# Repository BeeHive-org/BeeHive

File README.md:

# BeeHive - a flexible platform for connecting different sensors and actuators

## Intro

This project started as a collaboration between [Ihor Sobianin](https://github.com/isobianin/) and [Andre Chagas](https://github.com/amchagas/), after some chats about improving the [FlyPi design](https://github.com/amchagas/flypi). 

## Hardware 

The idea here is to make a very flexible hardware system that is easy to expand/customize for lab applications. The very initial implementation consists of:
- a hub PCB - which contains:
   -  2 voltage regulators that step down voltage from 12V to 5V and supply these 3 voltages to specific pins throughout the board.
   -  a central slot for an [ESP32 WROOM](https://www.espressif.com/sites/default/files/documentation/esp32-wroom-32_datasheet_en.pdf) and the breakout of all its pins into JST connectors.
   - Two Mikroe MikroBus connectors (https://www.mikroe.com/mikrobus).
   - Two Sparkfun Qwiic connectore (https://www.sparkfun.com/qwiic).
   - A 3.3V onboard voltage regulator.

-  4 switch array with an [TPIC6B595 shift register](https://www.ti.com/lit/ds/symlink/tpic6b595.pdf) and transistors.

-  8 switch array with an [TPIC6B595 shift register](https://www.ti.com/lit/ds/symlink/tpic6b595.pdf) and transistors.

-  12V5A breakout which is based on simple barrel jack connector and JST connectors

-  power supply which are based on the [LM2596 T5](https://www.ti.com/lit/ds/symlink/lm2596.pdf) a step down switching regulator
For more details see [current design](#the-current-design) section below.  

## Software

On the software side of things we are initially running micropython, as this will offer a low entry barrier for researchers (as Python is more and more the chosen language for much of the scientific stack).

- The current implementation runs stock micropython with [OSC library](https://github.com/SpotlightKid/micropython-osc) for communication, as this will allow easy integration with [Bonsai-RX](https://bonsai-rx.org/), a powerful piece of software that has integrations with other interesting open source tools for science, such as [open ephys](https://open-ephys.org/), [DeepLab Cut](http://www.mousemotorlab.org/deeplabcut) and other proprietary but useful tools, like high speed cameras, National Instruments DAQ systems. 

- The main wish software wise for this project is to make it compatible with [Labthings](https://github.com/labthings).

---

## The current design

### The main hub:

#### Schematics

#### PCB

### The power supply module:

#### Schematics

#### PCB

### The transistor-switch hub for 8 devices:

#### Schematics

#### PCB

---

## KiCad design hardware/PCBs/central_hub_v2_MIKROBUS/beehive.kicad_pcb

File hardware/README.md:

In this folder users & collaborators will find designs and considerations about the hardware parts being developed in this project. 

### hub_PCB:
- the central part of the system, is mainly a breakout board for the ESP32 being used and two built in power supplies. 

The pin mapping of the ESP32 controller and our board can be seen here:

Using table 2 of this [manual](https://www.espressif.com/sites/default/files/documentation/esp32-wroom-32_datasheet_en.pdf) we can see all the options for each pin.

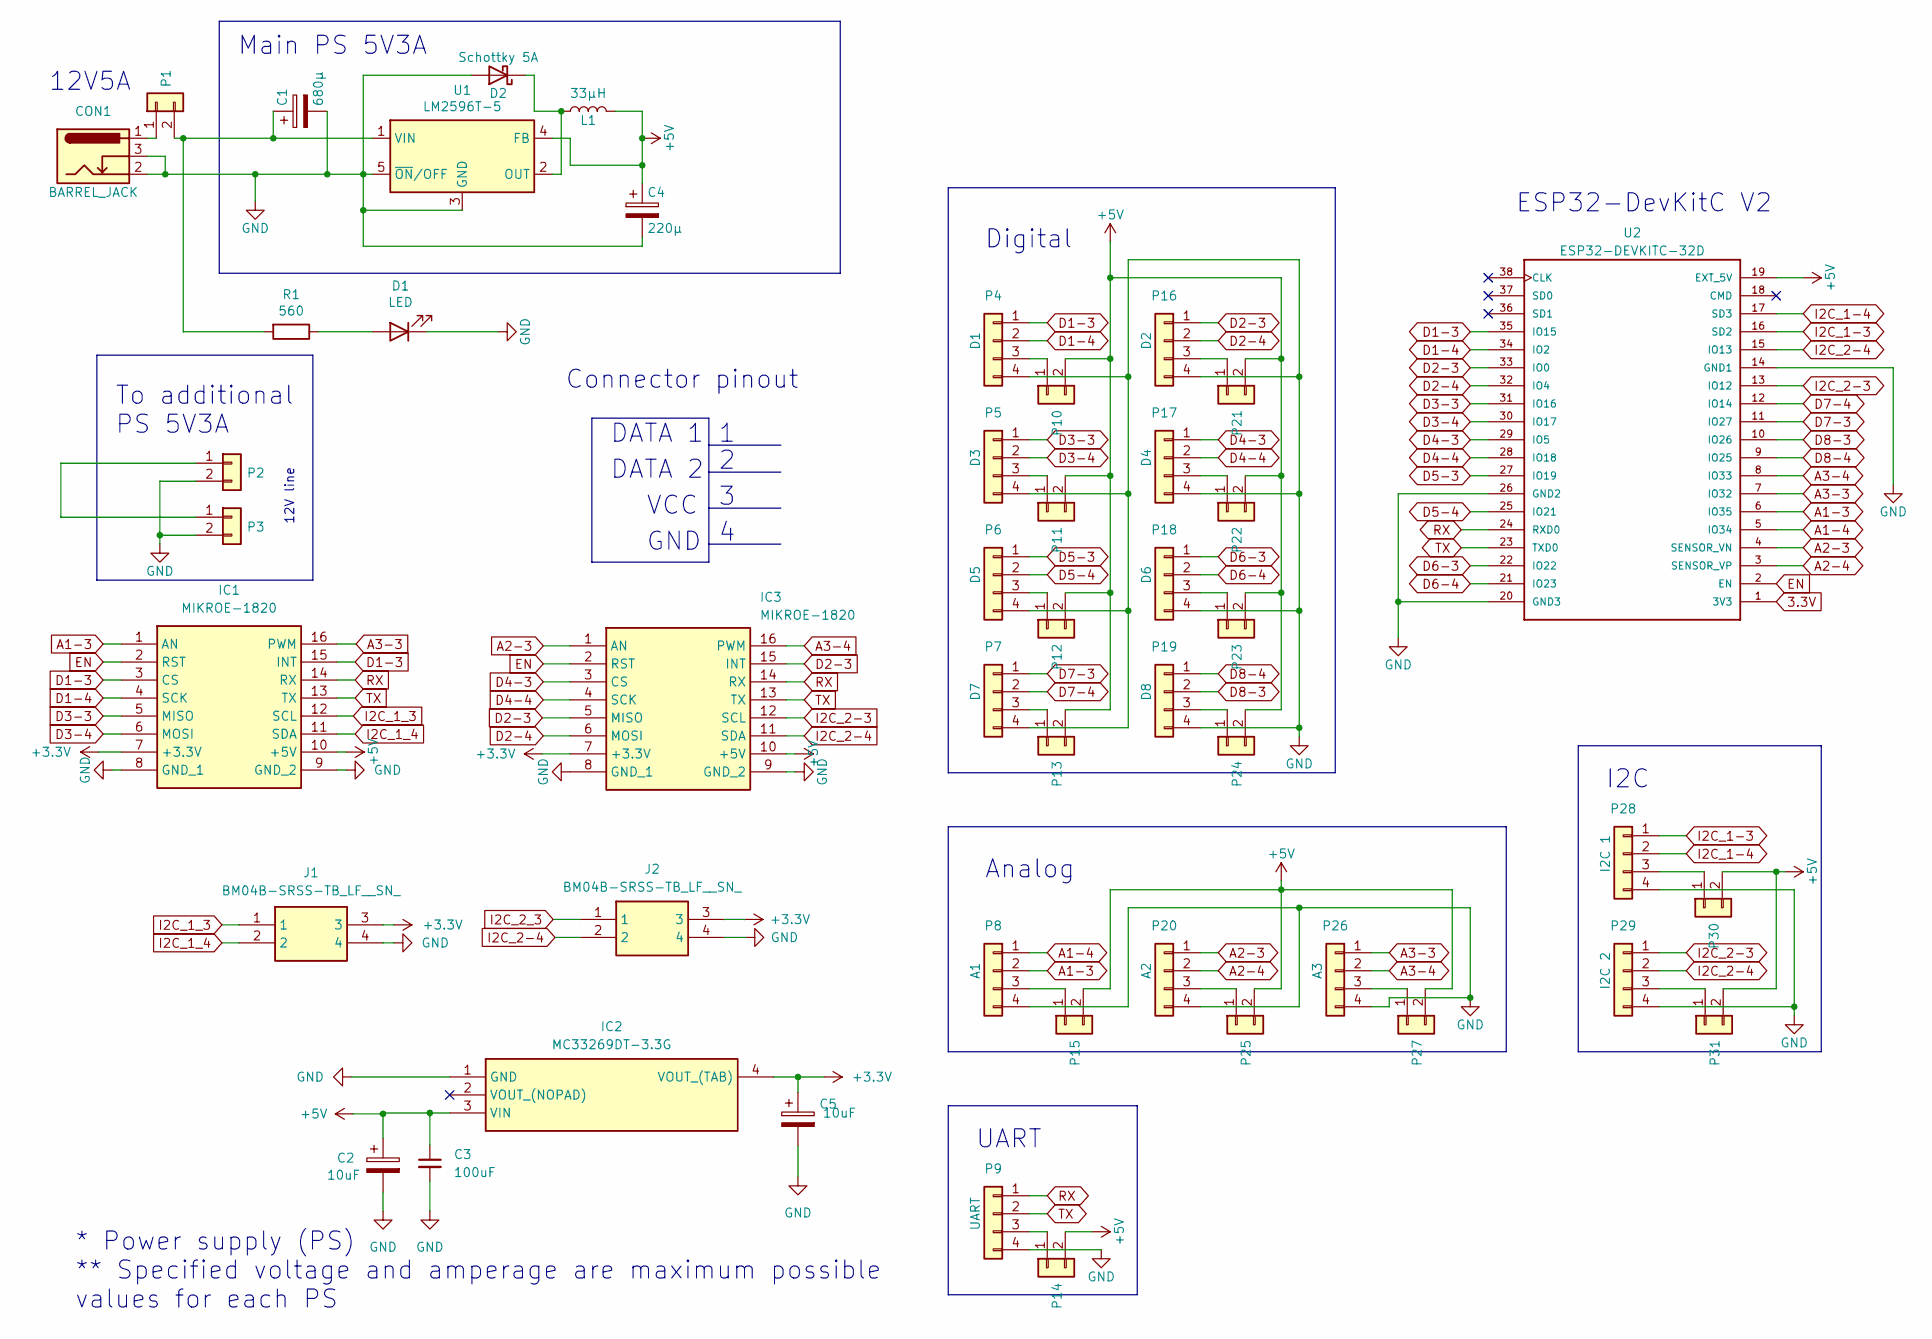
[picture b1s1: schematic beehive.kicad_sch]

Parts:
C1: 680µ; C_Radial_D10_L21_P5
C2, C5: 10uF; C_1206_3216Metric_Pad1.33x1.80mm_HandSolder
C3: 100uF; C_1206_3216Metric_Pad1.33x1.80mm_HandSolder
C4: 220µ; C_Radial_D8_L13_P3.8
CON1: BARREL_JACK; BarrelJack_Horizontal
D1: LED; LED_D3.0mm
D2: Schottky 5A; Diode_DO-201AD_Horizontal_RM15
IC1, IC3: MIKROE-1820; MIKROE1820; Mouser Part Number 932-MIKROE-1820
IC2: MC33269DT-3.3G; TO229P990X238-4N; Mouser Part Number 863-MC33269DT-3.3G
J1, J2: BM04B-SRSS-TB_LF__SN_; SM04B-SRSS-TB_LFSN_; Manufacturer_Part_Number BM04B-SRSS-TB(LF)(SN)
L1: 33µH; Neosid_Inductor_MA-Bs75
P1, P2, P3, P10, P11, P12, P13, P14, P15, P21, P22, P23, P24, P25, P27, P30, P31: Conn_01x02; JST_XH_B2B-XH-A_1x02_P2.50mm_Vertical
P4: D1; JST_XH_B04B-XH-A_04x2.50mm_Straight
P5: D3; JST_XH_B04B-XH-A_04x2.50mm_Straight
P6: D5; JST_XH_B04B-XH-A_04x2.50mm_Straight
P7: D7; JST_XH_B04B-XH-A_04x2.50mm_Straight
P8: A1; JST_XH_B04B-XH-A_04x2.50mm_Straight
P9: UART; JST_XH_B04B-XH-A_04x2.50mm_Straight
P16: D2; JST_XH_B04B-XH-A_04x2.50mm_Straight
P17: D4; JST_XH_B04B-XH-A_04x2.50mm_Straight
P18: D6; JST_XH_B04B-XH-A_04x2.50mm_Straight
P19: D8; JST_XH_B04B-XH-A_04x2.50mm_Straight
P20: A2; JST_XH_B04B-XH-A_04x2.50mm_Straight
P26: A3; JST_XH_B04B-XH-A_04x2.50mm_Straight
P28: I2C 1; JST_XH_B04B-XH-A_04x2.50mm_Straight
P29: I2C 2; JST_XH_B04B-XH-A_04x2.50mm_Straight
R1: 560; R_Box_L13.0mm_W4.0mm_P9.00mm
U1: LM2596T-5; TO-220-5_P3.4x3.7mm_StaggerOdd_Lead3.8mm_Vertical
U2: ESP32-DEVKITC-32D; MODULE_ESP32-DEVKITC-32D

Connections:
3.3V: U2.1 (3V3)
+3.3V: C5.1, IC1.7 (+3.3V), IC2.4 (VOUT_(TAB)), IC3.7 (+3.3V), J1.3, J2.3
A1-3: IC1.1 (AN), P8.2, U2.6 (IO35)
A1-4: P8.1, U2.5 (IO34)
A2-3: IC3.1 (AN), P20.1, U2.4 (SENSOR_VN)
A2-4: P20.2, U2.3 (SENSOR_VP)
A3-3: IC1.16 (PWM), P26.1, U2.7 (IO32)
A3-4: IC3.16 (PWM), P26.2, U2.8 (IO33)
D1-3: IC1.3 (CS), IC1.15 (INT), P4.1, U2.35 (IO15)
D1-4: IC1.4 (SCK), P4.2, U2.34 (IO2)
D2-3: IC3.5 (MISO), IC3.15 (INT), P16.1, U2.33 (IO0)
D2-4: IC3.6 (MOSI), P16.2, U2.32 (IO4)
D3-3: IC1.5 (MISO), P5.1, U2.31 (IO16)
D3-4: IC1.6 (MOSI), P5.2, U2.30 (IO17)
D4-3: IC3.3 (CS), P17.1, U2.29 (IO5)
D4-4: IC3.4 (SCK), P17.2, U2.28 (IO18)
D5-3: P6.1, U2.27 (IO19)
D5-4: P6.2, U2.25 (IO21)
D6-3: P18.1, U2.22 (IO22)
D6-4: P18.2, U2.21 (IO23)
D7-3: P7.1, U2.11 (IO27)
D7-4: P7.2, U2.12 (IO14)
D8-3: P19.2, U2.10 (IO26)
D8-4: P19.1, U2.9 (IO25)
EN: IC1.2 (RST), IC3.2 (RST), U2.2 (EN)
GND: C1.2, C2.2, C3.2, C4.2, C5.2, CON1.2, CON1.3, D1.1 (K), D2.2 (A), IC1.8 (GND_1), IC1.9 (GND_2), IC2.1 (GND), IC3.8 (GND_1), IC3.9 (GND_2), J1.4, J2.4, P2.2, P3.2, P4.4, P5.4, P6.4, P7.4, P8.4, P9.4, P16.4, P17.4, P18.4, P19.4, P20.4, P26.4, P28.4, P29.4, U1.3 (GND), U1.5 (~ON/OFF), U2.14 (GND1), U2.20 (GND3), U2.26 (GND2)
I2C_1-3: P28.1, U2.16 (SD2)
I2C_1-4: P28.2, U2.17 (SD3)
I2C_1_3: IC1.12 (SCL), J1.1
I2C_1_4: IC1.11 (SDA), J1.2
I2C_2-3: IC3.12 (SCL), P29.1, U2.13 (IO12)
I2C_2-4: IC3.11 (SDA), J2.2, P29.2, U2.15 (IO13)
I2C_2_3: J2.1
unnamed: D1.2 (A), R1.1
unnamed: D2.1 (K), L1.1, U1.2 (OUT)
unnamed: CON1.1, P1.1
unnamed: P2.1, P3.1
unnamed: P4.3, P10.1
unnamed: P5.3, P11.1
unnamed: P6.3, P12.1
unnamed: P7.3, P13.1
unnamed: P9.3, P14.1
unnamed: P8.3, P15.1
unnamed: P16.3, P21.1
unnamed: P17.3, P22.1
unnamed: P18.3, P23.1
unnamed: P19.3, P24.1
unnamed: P20.3, P25.1
unnamed: P26.3, P27.1
unnamed: P28.3, P30.1
unnamed: P29.3, P31.1
RX: IC1.14 (RX), IC3.14 (RX), P9.1, U2.24 (RXD0)
TX: IC1.13 (TX), IC3.13 (TX), P9.2, U2.23 (TXD0)

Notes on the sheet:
Connector pinout
12V line
To additional PS 5V3A
VCC
Analog
12V5A
DATA 1
GND
ESP32-DevKitC V2
Main PS 5V3A
* Power supply (PS) ** Specified voltage and amperage are maximum possible values for each PS
DATA 2
I2C
UART
Digital

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
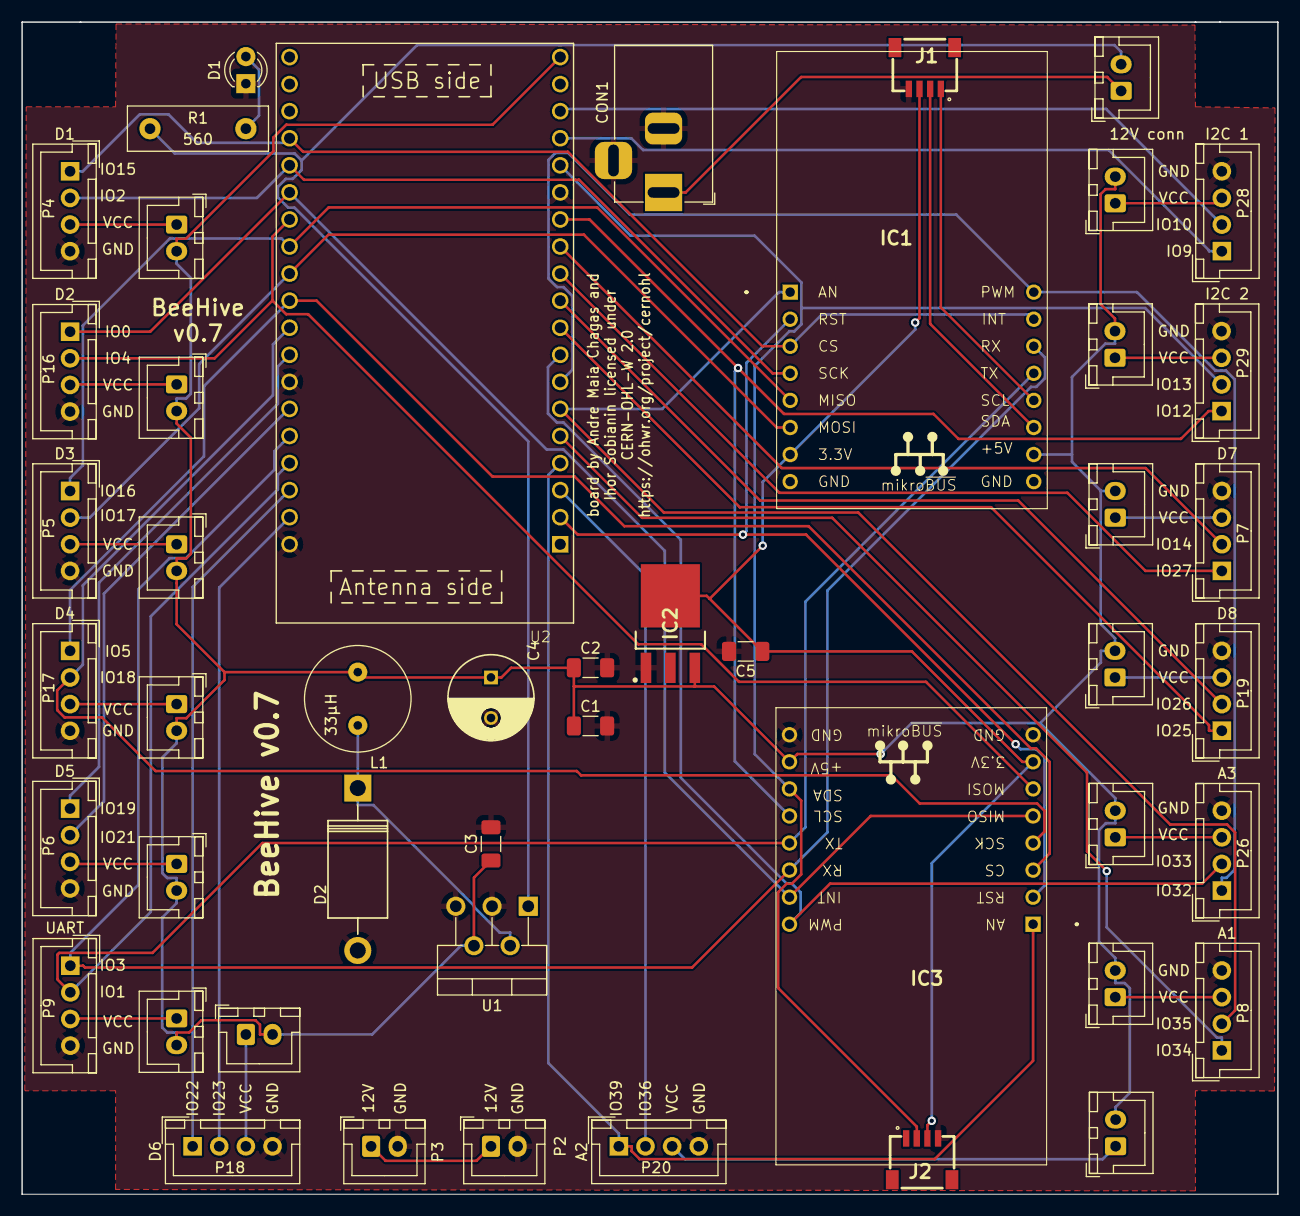
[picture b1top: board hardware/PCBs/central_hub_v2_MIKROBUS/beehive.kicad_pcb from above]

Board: 2 copper layers, 117.8 x 110.0 mm, 48 parts (0 on the bottom side), 53 nets.

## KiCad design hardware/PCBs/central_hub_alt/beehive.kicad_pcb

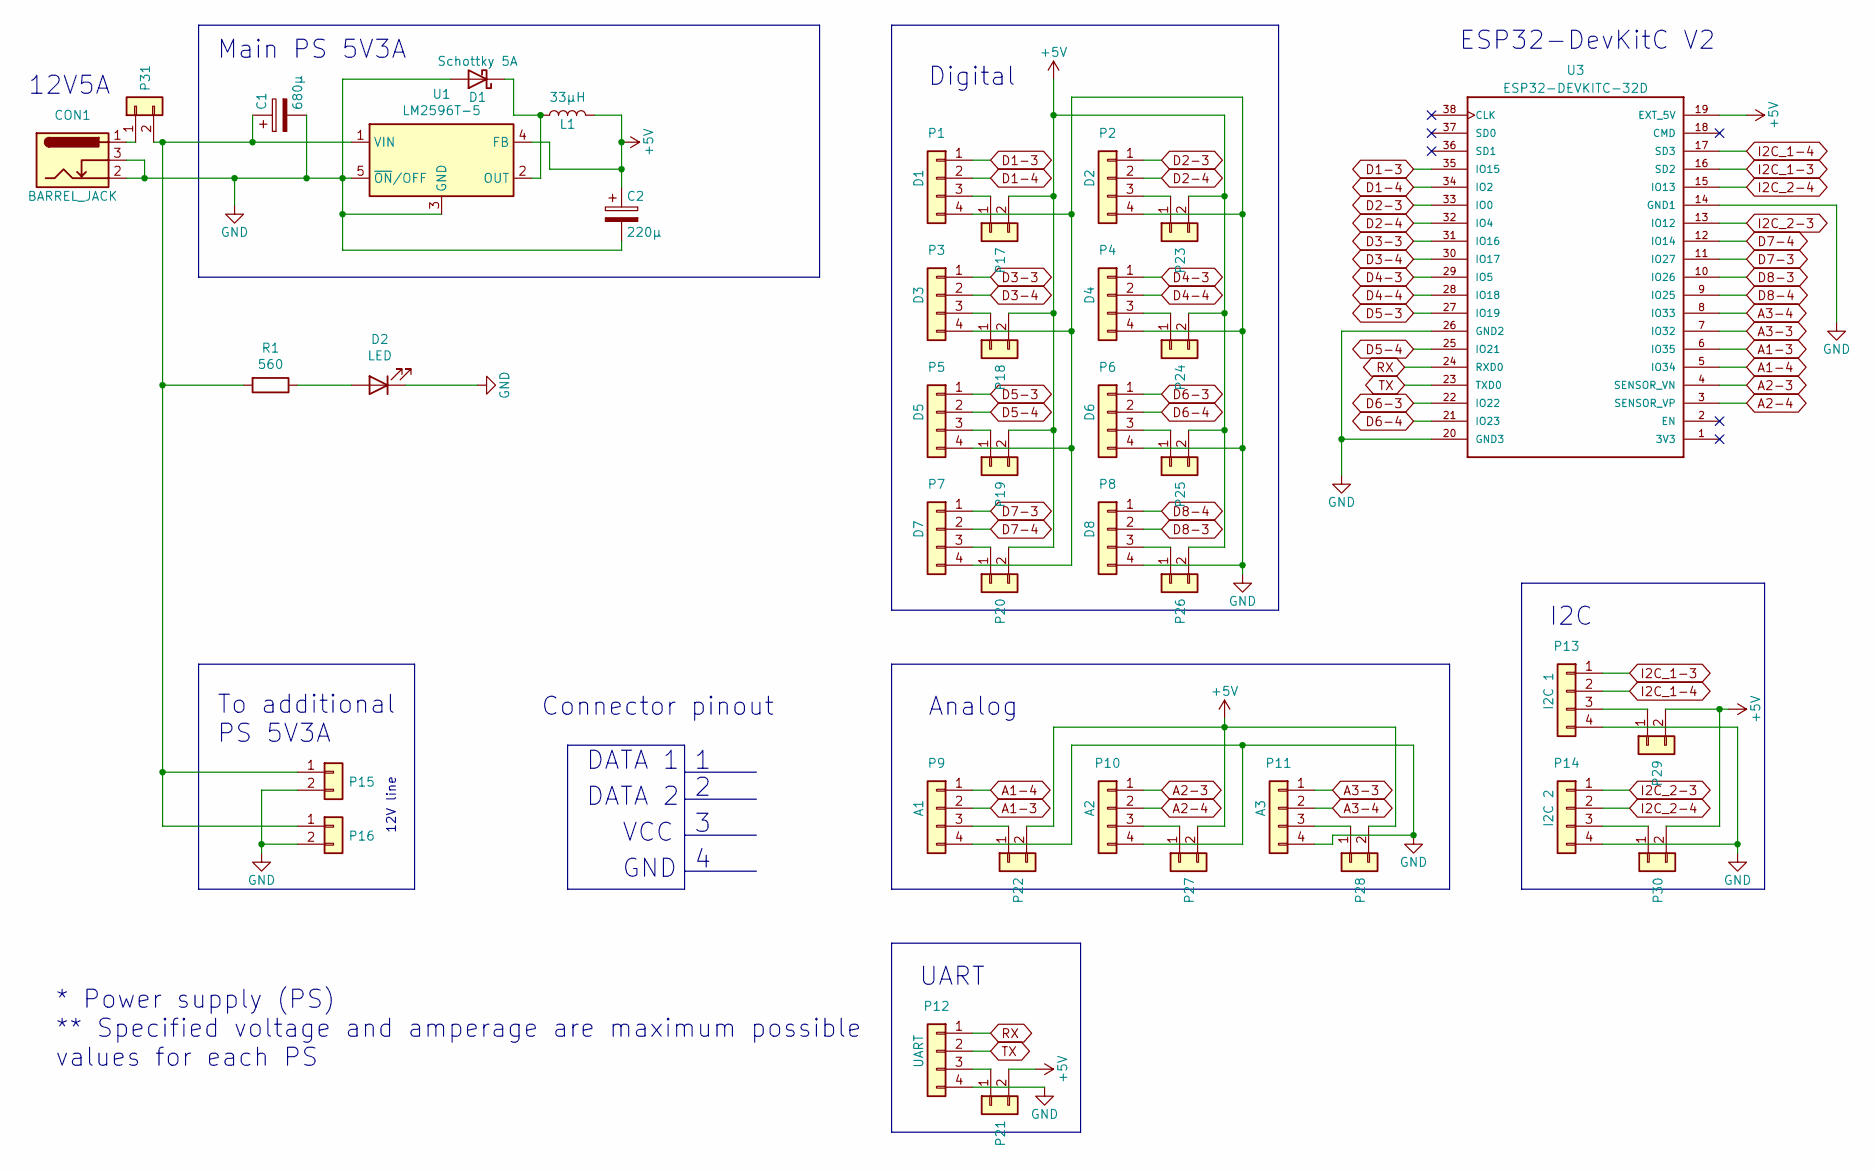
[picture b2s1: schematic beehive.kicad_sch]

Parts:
C1: 680µ; C_Radial_D10_L21_P5
C2: 220µ; C_Radial_D8_L13_P3.8
CON1: BARREL_JACK; BarrelJack_Horizontal
D1: Schottky 5A; Diode_DO-201AD_Horizontal_RM15
D2: LED; LED_D3.0mm
L1: 33µH; Neosid_Inductor_MA-Bs75
P1: D1; JST_XH_B04B-XH-A_04x2.50mm_Straight
P2: D2; JST_XH_B04B-XH-A_04x2.50mm_Straight
P3: D3; JST_XH_B04B-XH-A_04x2.50mm_Straight
P4: D4; JST_XH_B04B-XH-A_04x2.50mm_Straight
P5: D5; JST_XH_B04B-XH-A_04x2.50mm_Straight
P6: D6; JST_XH_B04B-XH-A_04x2.50mm_Straight
P7: D7; JST_XH_B04B-XH-A_04x2.50mm_Straight
P8: D8; JST_XH_B04B-XH-A_04x2.50mm_Straight
P9: A1; JST_XH_B04B-XH-A_04x2.50mm_Straight
P10: A2; JST_XH_B04B-XH-A_04x2.50mm_Straight
P11: A3; JST_XH_B04B-XH-A_04x2.50mm_Straight
P12: UART; JST_XH_B04B-XH-A_04x2.50mm_Straight
P13: I2C 1; JST_XH_B04B-XH-A_04x2.50mm_Straight
P14: I2C 2; JST_XH_B04B-XH-A_04x2.50mm_Straight
P15, P16, P17, P18, P19, P20, P21, P22, P23, P24, P25, P26, P27, P28, P29, P30, P31: Conn_01x02; JST_XH_B2B-XH-A_1x02_P2.50mm_Vertical
R1: 560; R_Box_L13.0mm_W4.0mm_P9.00mm
U1: LM2596T-5; TO-220-5_P3.4x3.7mm_StaggerOdd_Lead3.8mm_Vertical
U3: ESP32-DEVKITC-32D; MODULE_ESP32-DEVKITC-32D

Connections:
+5V: C2.1, L1.2, P17.2, P18.2, P19.2, P20.2, P21.2, P22.2, P23.2, P24.2, P25.2, P26.2, P27.2, P28.2, P29.2, P30.2, U1.4 (FB), U3.19 (EXT_5V)
A1-3: P9.2, U3.6 (IO35)
A1-4: P9.1, U3.5 (IO34)
A2-3: P10.1, U3.4 (SENSOR_VN)
A2-4: P10.2, U3.3 (SENSOR_VP)
A3-3: P11.1, U3.7 (IO32)
A3-4: P11.2, U3.8 (IO33)
D1-3: P1.1, U3.35 (IO15)
D1-4: P1.2, U3.34 (IO2)
D2-3: P2.1, U3.33 (IO0)
D2-4: P2.2, U3.32 (IO4)
D3-3: P3.1, U3.31 (IO16)
D3-4: P3.2, U3.30 (IO17)
D4-3: P4.1, U3.29 (IO5)
D4-4: P4.2, U3.28 (IO18)
D5-3: P5.1, U3.27 (IO19)
D5-4: P5.2, U3.25 (IO21)
D6-3: P6.1, U3.22 (IO22)
D6-4: P6.2, U3.21 (IO23)
D7-3: P7.1, U3.11 (IO27)
D7-4: P7.2, U3.12 (IO14)
D8-3: P8.2, U3.10 (IO26)
D8-4: P8.1, U3.9 (IO25)
GND: C1.2, C2.2, CON1.2, CON1.3, D1.2 (A), D2.1 (K), P1.4, P2.4, P3.4, P4.4, P5.4, P6.4, P7.4, P8.4, P9.4, P10.4, P11.4, P12.4, P13.4, P14.4, P15.2, P16.2, U1.3 (GND), U1.5 (~ON/OFF), U3.14 (GND1), U3.20 (GND3), U3.26 (GND2)
I2C_1-3: P13.1, U3.16 (SD2)
I2C_1-4: P13.2, U3.17 (SD3)
I2C_2-3: P14.1, U3.13 (IO12)
I2C_2-4: P14.2, U3.15 (IO13)
unnamed: C1.1, P15.1, P16.1, P31.2, R1.2, U1.1 (VIN)
unnamed: CON1.1, P31.1
unnamed: D1.1 (K), L1.1, U1.2 (OUT)
unnamed: D2.2 (A), R1.1
unnamed: P1.3, P17.1
unnamed: P2.3, P23.1
unnamed: P10.3, P27.1
unnamed: P11.3, P28.1
unnamed: P12.3, P21.1
unnamed: P13.3, P29.1
unnamed: P14.3, P30.1
unnamed: P3.3, P18.1
unnamed: P5.3, P19.1
unnamed: P7.3, P20.1
unnamed: P9.3, P22.1
unnamed: P4.3, P24.1
unnamed: P6.3, P25.1
unnamed: P8.3, P26.1
RX: P12.1, U3.24 (RXD0)
TX: P12.2, U3.23 (TXD0)

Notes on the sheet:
Connector pinout
12V line
To additional PS 5V3A
VCC
Analog
12V5A
DATA 1
GND
ESP32-DevKitC V2
Main PS 5V3A
* Power supply (PS) ** Specified voltage and amperage are maximum possible values for each PS
DATA 2
I2C
UART
Digital

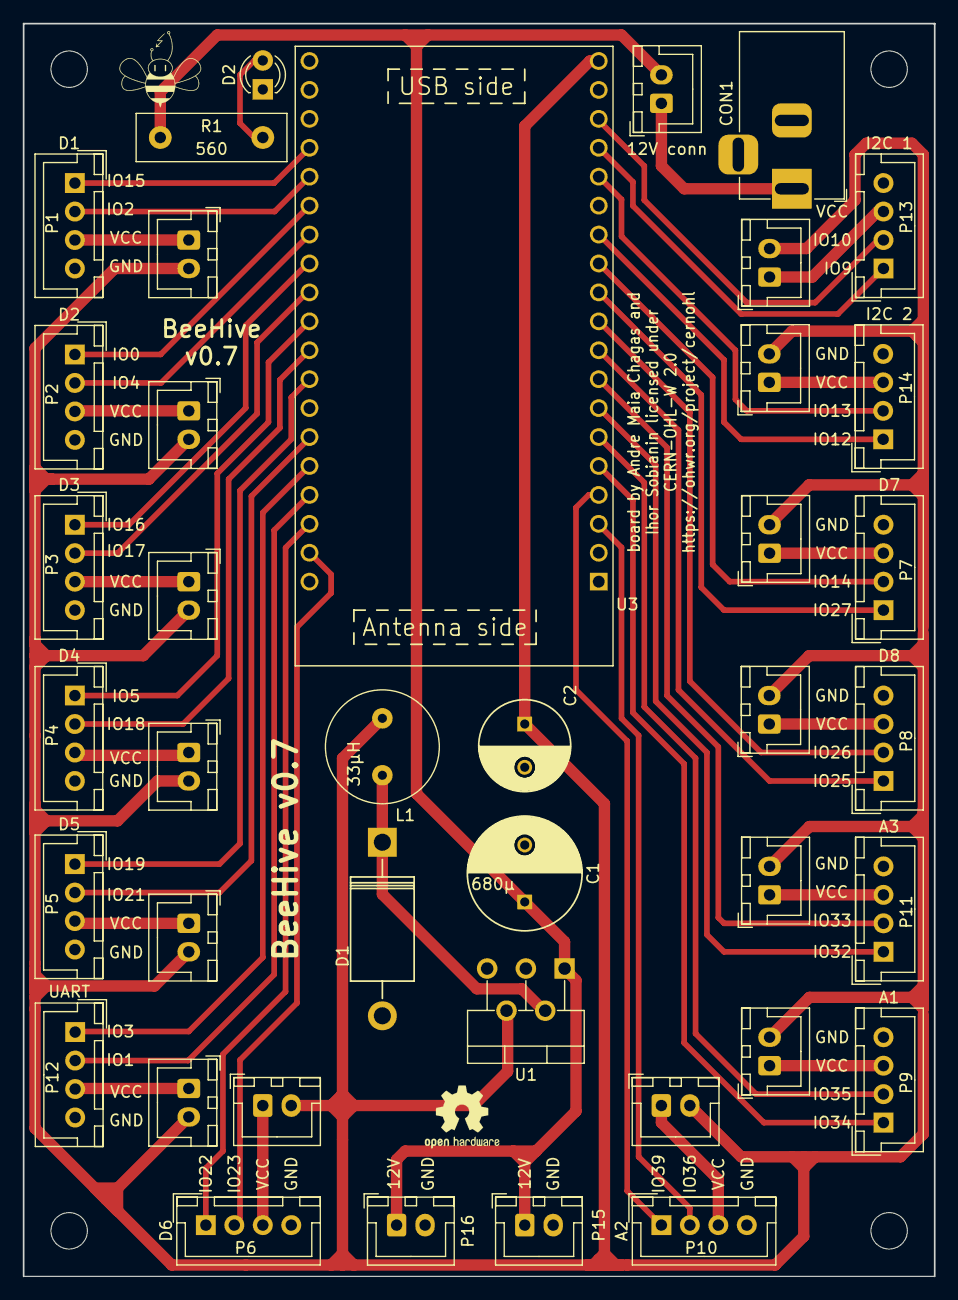
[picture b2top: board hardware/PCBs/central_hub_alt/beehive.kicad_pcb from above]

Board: 2 copper layers, 80.0 x 110.0 mm, 41 parts (0 on the bottom side), 48 nets.

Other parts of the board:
 : OSHW-Logo2_7.3x6mm_SilkScreen

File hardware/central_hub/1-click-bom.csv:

References,Qty,Description,Manufacturer,MPN,Manufacturer,MPN,Manufacturer,MPN,Manufacturer,MPN,Manufacturer,MPN,Digikey,Mouser,RS,Newark,Farnell
U1;,1,LM2596 5v,ITO-220,Texas Instruments,Texas Instruments,LM2596T-5.0/NOPB,,,,,,,LM2596T-5.0/NOPB-ND,926LM2596T5.0/NOPB,5333743,,3008166
U3;,1,ESP32-DevKitC-VIB,,,,,,,,,,,,,,,
P1;P2;P3;P4;P5;P6;P7;P8;P9;P10;P11;P12;P13;P14;,14,CONN HEADER XH TOP 4POS 2.5MM,JST,B4B-XH-A (LF)(SN),,,,,,,,,455-2249-ND,,8201551,,1516278
P15;P16,2,CONN HEADER XH TOP 2POS 2.5MM,JST,B2B-XH-A (LF)(SN),,,,,,,,,455-2247-ND,,820-1554,,1516276
L1;,1,INDUCTOR 33µH Neosid MA-Bs75,Bourns,RLB0914-330KL,Bourns,RLB9012-330KL,,,,,,,RLB9012-330KL-ND,652RLB0914330KL,8118853,,2309242
J1;,1,USB A Vertical,FCI,73725-0110BLF,Molex,48204-0001,,,,,,,609-1041-ND,649737250110BLF,7710048,,2782046
D1;,1,Diode Schottky 5A DO-201AD,Vishay,1N5822-E3/73,Zetex,SB5100-T,,,,,,,1N5822-E3/73GICT-ND,6251N5822E3/73,7514843,,1336553
CON1;,1,2.1mm socket,Cliff,FC68148 DC10A,Lumberg,NEB 21 R,Cliff,FC68148,Gravitech,CON-SOCJ-2155,Parallax,452-00007,SC1313-ND,992CONSOCJ2155,5051609,,1217037
C1;,1,680µF Capacitor,Rubycon,16ZL680MEFC10X16,Panasonic,EEU-FC1A681,Panasonic,EEU-FP1E681,,,,,1189-3978-ND,667EEUFP1E681,1793151,,2911616
C2;,1,CAP ALUM 220UF 20% 25V RADIAL,Panasonic,EEU-FM1E221,Panasonic,ECA-1CM221B,Panasonic,ECE-A0GKS221,Panasonic,EEU-EB1A221S,,,P13456-ND,667ECA1CM221B,7472036,,9451099

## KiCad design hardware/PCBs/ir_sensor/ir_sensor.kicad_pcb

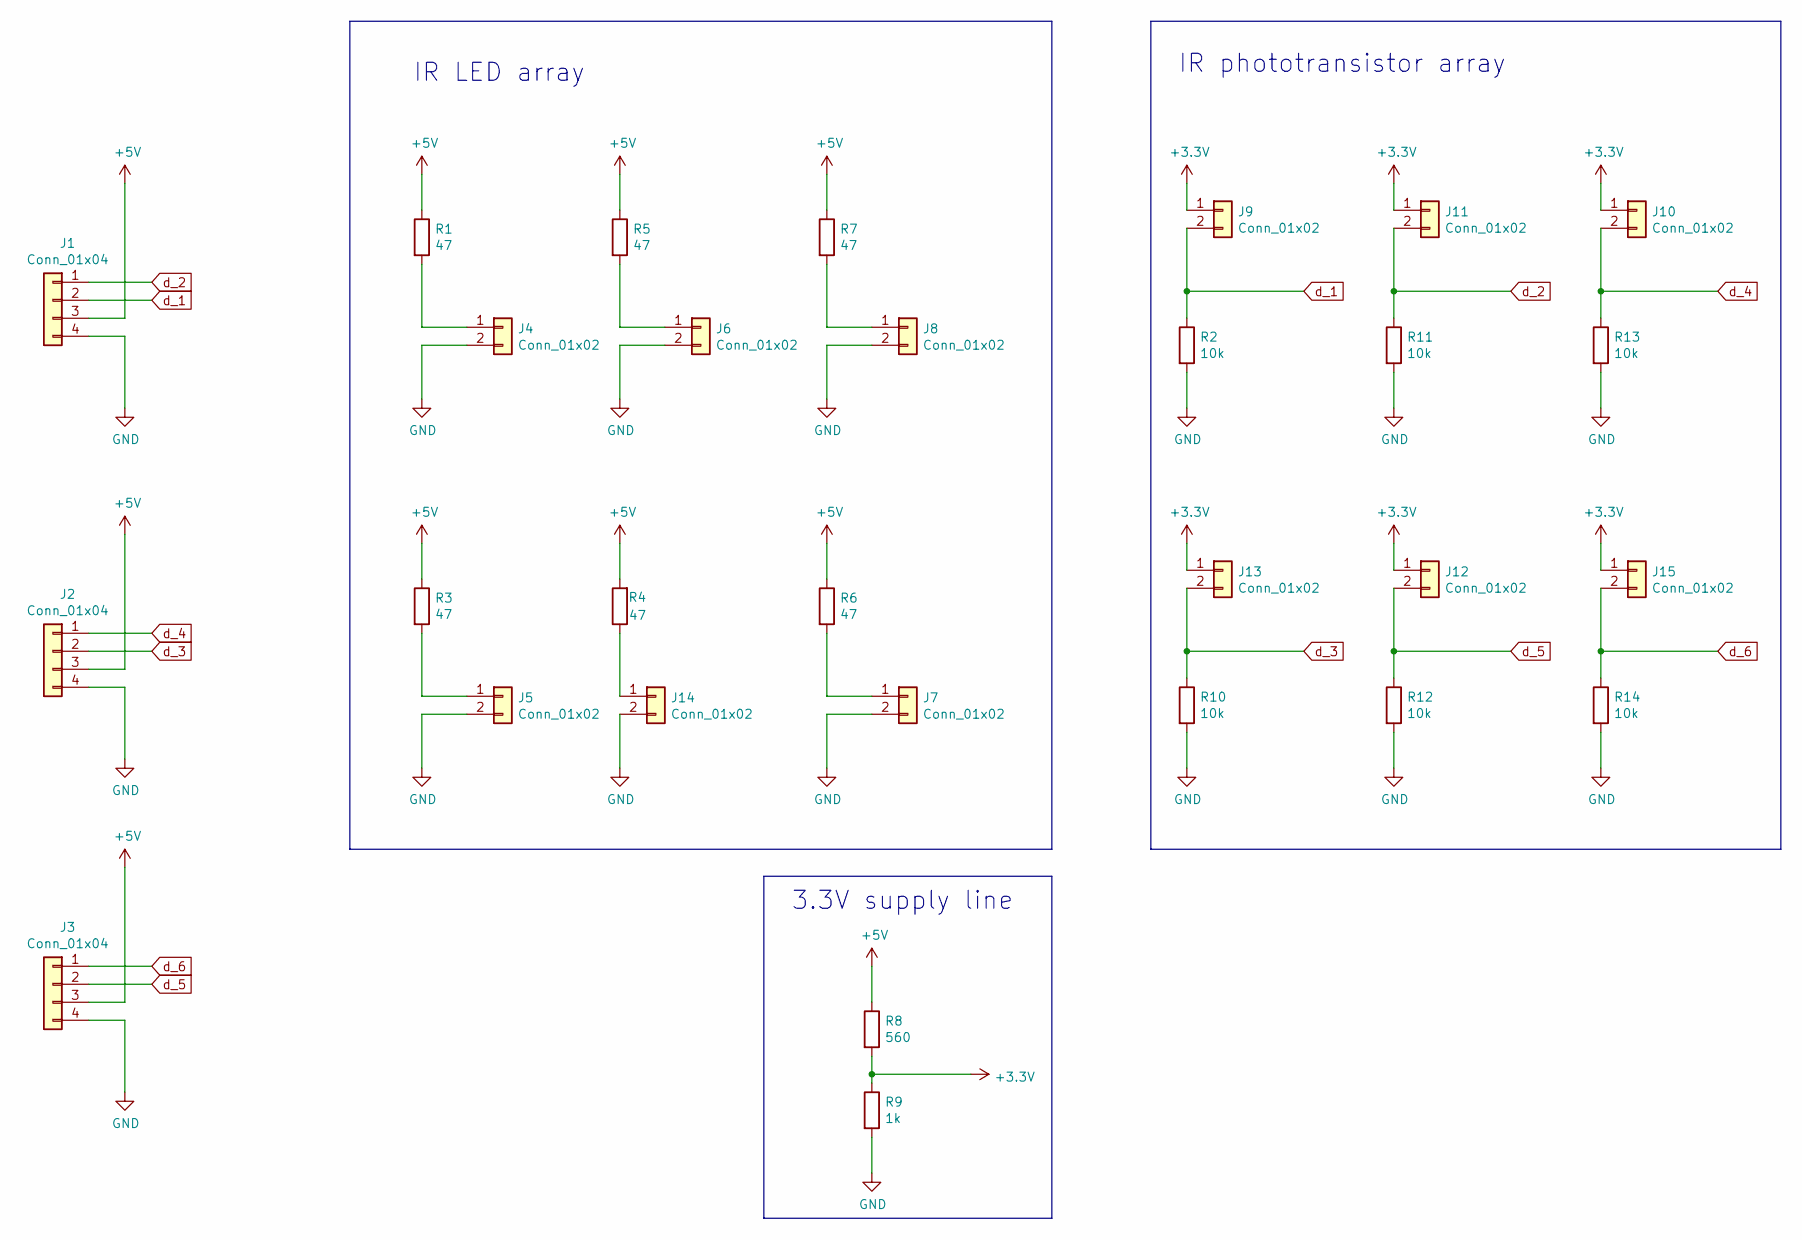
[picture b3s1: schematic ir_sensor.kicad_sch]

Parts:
J1, J2, J3: Conn_01x04; JST_XH_B4B-XH-A_1x04_P2.50mm_Vertical
J4, J5, J6, J7, J8, J9, J10, J11, J12, J13, J14, J15: Conn_01x02; JST_XH_B2B-XH-A_1x02_P2.50mm_Vertical
R1, R3, R4, R5, R6, R7: 47; R_Box_L13.0mm_W4.0mm_P9.00mm
R2, R10, R11, R12, R13, R14: 10k; R_Box_L13.0mm_W4.0mm_P9.00mm
R8: 560; R_Box_L13.0mm_W4.0mm_P9.00mm
R9: 1k; R_Box_L13.0mm_W4.0mm_P9.00mm

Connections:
+3V3: J9.1, J10.1, J11.1, J12.1, J13.1, J15.1, R8.2, R9.1
+5V: J1.3, J2.3, J3.3, R1.1, R3.1, R4.2, R5.1, R6.1, R7.1, R8.1
GND: J1.4, J2.4, J3.4, J4.2, J5.2, J6.2, J7.2, J8.2, J14.2, R2.2, R9.2, R10.2, R11.2, R12.2, R13.2, R14.2
unnamed: J4.1, R1.2
unnamed: J5.1, R3.2
unnamed: J6.1, R5.2
unnamed: J7.1, R6.2
unnamed: J8.1, R7.2
unnamed: J14.1, R4.1
d_1: J1.2, J9.2, R2.1
d_2: J1.1, J11.2, R11.1
d_3: J2.2, J13.2, R10.1
d_4: J2.1, J10.2, R13.1
d_5: J3.2, J12.2, R12.1
d_6: J3.1, J15.2, R14.1

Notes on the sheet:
3.3V supply line
IR LED array
IR phototransistor array

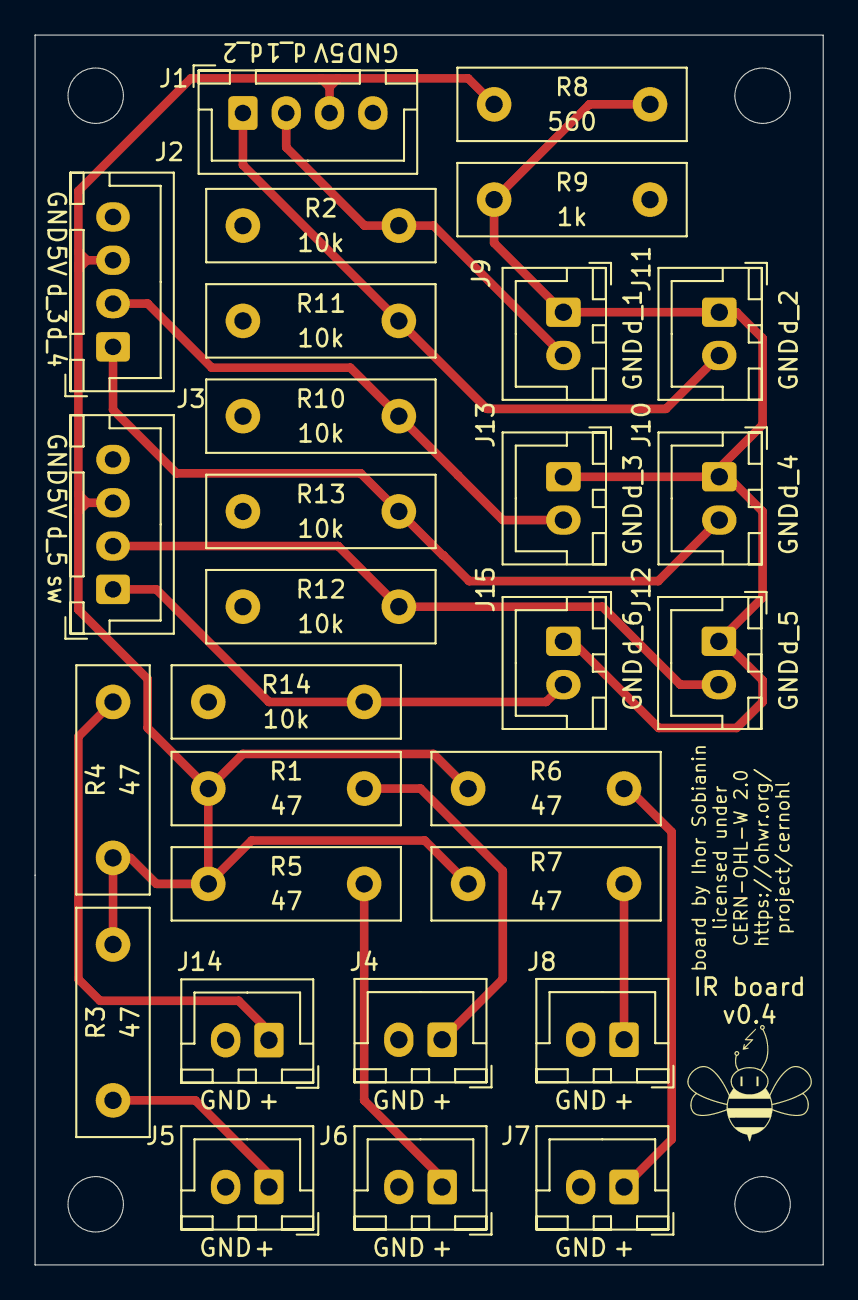
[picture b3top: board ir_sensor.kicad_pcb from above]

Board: 2 copper layers, 45.5 x 71.0 mm, 29 parts (0 on the bottom side), 15 nets.

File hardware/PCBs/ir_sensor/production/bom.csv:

Designator,Footprint,Quantity,Value,LCSC Part #
J1,JST_XH_B4B-XH-A_1x04_P2.50mm_Vertical,1,Conn_01x04,
R1,R_Box_L13.0mm_W4.0mm_P9.00mm,1,47,
R2,R_Box_L13.0mm_W4.0mm_P9.00mm,1,10k,
J2,JST_XH_B4B-XH-A_1x04_P2.50mm_Vertical,1,Conn_01x04,
J3,JST_XH_B4B-XH-A_1x04_P2.50mm_Vertical,1,Conn_01x04,
J4,JST_XH_B2B-XH-A_1x02_P2.50mm_Vertical,1,Conn_01x02,
J5,JST_XH_B2B-XH-A_1x02_P2.50mm_Vertical,1,Conn_01x02,
J6,JST_XH_B2B-XH-A_1x02_P2.50mm_Vertical,1,Conn_01x02,
J7,JST_XH_B2B-XH-A_1x02_P2.50mm_Vertical,1,Conn_01x02,
J8,JST_XH_B2B-XH-A_1x02_P2.50mm_Vertical,1,Conn_01x02,
J9,JST_XH_B2B-XH-A_1x02_P2.50mm_Vertical,1,Conn_01x02,
J10,JST_XH_B2B-XH-A_1x02_P2.50mm_Vertical,1,Conn_01x02,
J11,JST_XH_B2B-XH-A_1x02_P2.50mm_Vertical,1,Conn_01x02,
J12,JST_XH_B2B-XH-A_1x02_P2.50mm_Vertical,1,Conn_01x02,
J13,JST_XH_B2B-XH-A_1x02_P2.50mm_Vertical,1,Conn_01x02,
R3,R_Box_L13.0mm_W4.0mm_P9.00mm,1,47,
R4,R_Box_L13.0mm_W4.0mm_P9.00mm,1,47,
R5,R_Box_L13.0mm_W4.0mm_P9.00mm,1,47,
R6,R_Box_L13.0mm_W4.0mm_P9.00mm,1,47,
R7,R_Box_L13.0mm_W4.0mm_P9.00mm,1,47,
R8,R_Box_L13.0mm_W4.0mm_P9.00mm,1,560,
R9,R_Box_L13.0mm_W4.0mm_P9.00mm,1,1k,
R10,R_Box_L13.0mm_W4.0mm_P9.00mm,1,10k,
R11,R_Box_L13.0mm_W4.0mm_P9.00mm,1,10k,
R12,R_Box_L13.0mm_W4.0mm_P9.00mm,1,10k,
R13,R_Box_L13.0mm_W4.0mm_P9.00mm,1,10k,
J14,JST_XH_B2B-XH-A_1x02_P2.50mm_Vertical,1,Conn_01x02,
J15,JST_XH_B2B-XH-A_1x02_P2.50mm_Vertical,1,Conn_01x02,
R14,R_Box_L13.0mm_W4.0mm_P9.00mm,1,10k,

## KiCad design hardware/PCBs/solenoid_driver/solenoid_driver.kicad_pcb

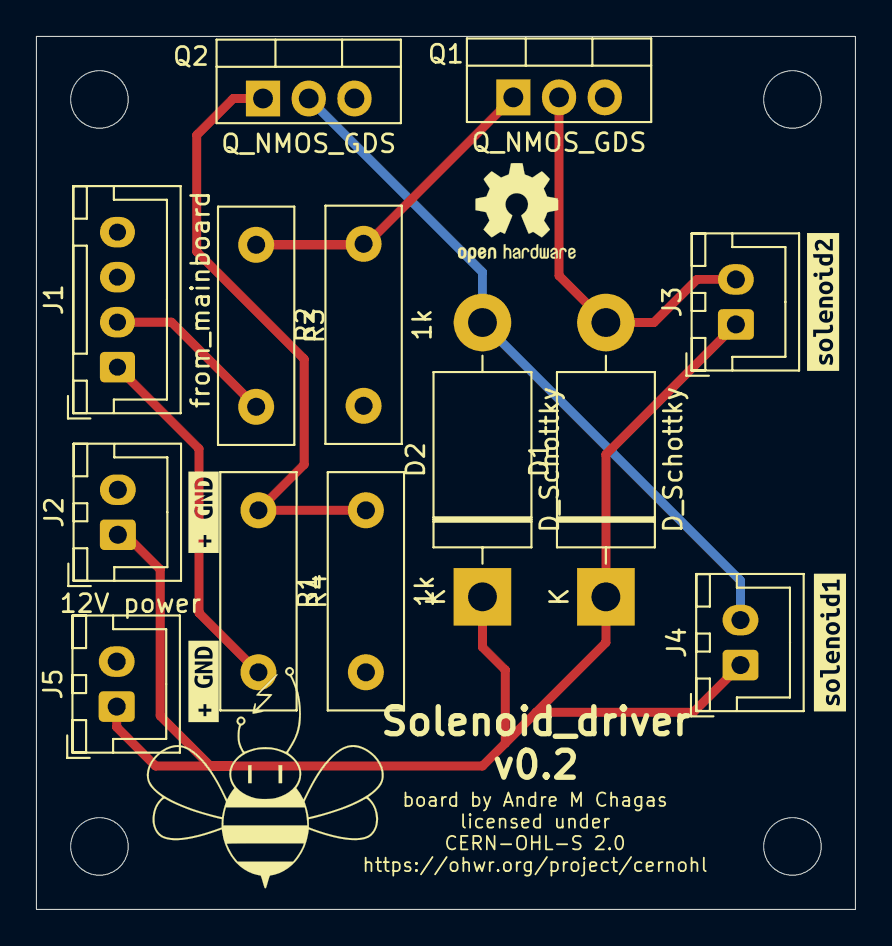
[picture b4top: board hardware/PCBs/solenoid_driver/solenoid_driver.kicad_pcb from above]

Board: 2 copper layers, 45.5 x 48.5 mm, 17 parts (0 on the bottom side), 8 nets.

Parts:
D1, D2: D_Schottky; D_DO-201AD_P15.24mm_Horizontal
J1: from_mainboard; JST_XH_B4B-XH-A_1x04_P2.50mm_Vertical
J2, J5: 12V power; JST_XH_B2B-XH-A_1x02_P2.50mm_Vertical
J3: to_solenoid2; JST_XH_B2B-XH-A_1x02_P2.50mm_Vertical
J4: to_solenoid1; JST_XH_B2B-XH-A_1x02_P2.50mm_Vertical
Q1, Q2: Q_NMOS_GDS; TO-220-3_Vertical
R1, R2: 1k; R_Box_L13.0mm_W4.0mm_P9.00mm
R3, R4: 47; R_Box_L13.0mm_W4.0mm_P9.00mm
kibuzzard-63063C94: G***; kibuzzard-63063C94
kibuzzard-63064E8E: G***; kibuzzard-63064E8E
kibuzzard-63064EFA: G***; kibuzzard-63064EFA
kibuzzard-63065932: G***; kibuzzard-63065932

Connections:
+12V: D1.1 (K), D2.1 (K), J2.1, J3.1, J4.1, J5.1
GND: J1.4, J2.2, J5.2, Q1.3 (S), Q2.3 (S), R1.1, R2.1
unnamed: D1.2 (A), J3.2, Q1.2 (D)
unnamed: D2.2 (A), J4.2, Q2.2 (D)
unnamed: Q1.1 (G), R2.2, R3.1
unnamed: Q2.1 (G), R1.2, R4.1
solenoid1: J1.1, R4.2
solenoid2: J1.2, R3.2

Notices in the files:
hardware/PCBs/central_hub_alt/beehive.kicad_pcb:
board by Andre Maia Chagas and
Ihor Sobianin licensed under
CERN-OHL-W 2.0
hardware/PCBs/solenoid_driver/solenoid_driver.kicad_pcb:
CERN-OHL-S 2.0
